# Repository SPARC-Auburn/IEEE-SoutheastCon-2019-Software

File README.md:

# Software Documentation

This is the software documentation for Auburn's IEEE Southeastcon 2019 Hardware Competition Team.  See the [main repository](https://github.com/SPARC-Auburn/IEEE-SoutheastCon-2019) for more general information.

## Robot Operating System (ROS)
The need for a simplified approach for localization sparked the switch to using the Robot Operating System (ROS.) ROS greatly simplifies complex localization, mapping, and pathfinding algorithms; all of which are incredibly essential to this competition, although, heed was taken at first because of the vast learning curve coupled with ROS. A very layman's explanation of ROS is that sensor data is input nodes, which house all the vital information for the sensors such as programs, readme files, or launch files. Nodes can talk to each other and request information, process the information, and send to another node. A graphical explanation of how our sensor nodes communicate is shown in Figure 1 below. We have four sensors; LIDAR, Camera, IMU, and encoders that create four ROS nodes. The LIDAR, IMU, and Encoder nodes all input into the localization node, this node coupled with the camera node create what we call the decision maker or essentially a path planner. The decision maker then outputs motor control commands to move the robot.

**Figure 1:** ROS Node Diagram

Figure 7 shows the resulting ROS graph of our implementation.  After testing, we determined the IMU was not adding any additional helpful information for localization so it was omitted from the final design.

**Figure 2:** ROS Node Diagram

## LIDAR and Localization

The LIDAR sensor is one of the main components of localization; this sensor acts sort of like a GPS for the robot. The YDLIDAR has a 360-degree scanning range with a 10-meter range. As stated previously and shown in Figure 1 the LIDAR will be a node, and this is one of two inputs into the localization node. ROS greatly simplifies the localization process as it already has the algorithms needed, one being AMCL. Adaptive Monte Carlo Localization is the process of tracking the pose of a robot against a known map, which is our case. AMCL takes in a map, LIDAR scan, and transform messages, and outputs pose estimates. As stated one of the first things we need to implement the AMCL algorithm is a known map, which is the competition field. Our original process of creating a map was creating a jpeg image and feeding it thru a python program launched within ROS to return a map. However, errors were given when adding the LIDAR scan data to the map.  To solve this issue, we had to pre-map the field with actual data using simultaneous location and mapping (SLAM).  This proved to be very effective, especially when there was a large skew in the field shape.  See Figure 3 for a view of the robot’s orientation and position plotted on a map in ROS.

**Figure 3:** RVIZ map with localized position and orientation

## Rotary Encoder and Odometry
In order to have more precise measurements in movement, we will use two capacitive encoders attached to the motors.  The encoders measure and count the turns of the motors, allowing us to know how far the robot will travel with one motor turn.  Using this alongside the localization and object detection, we would be able to move the robot the exact distance towards any detected object to ensure the robot picks up the object.  This will also prevent the robot from pushing any object into a position that would make it difficult to pick up.

The encoders are wired and read using a Teensy microcontroller.  The Teensy features built in interrupts that allow regular updates from the encoders.  This is required as the encoders measure rotations in ticks, these ticks update at a very fast frequency, requiring processing just as quickly.  The Teensy reads the encoder ticks and calculates the angular acceleration, which is then sent to the Raspberry Pi via serial.  
## Visual Detection
We are using the Raspberry Pi Camera Module to detect the debris objects.  By using the open-source computer vision library, the Pi can extrapolate the debris’s pixel location, pixel size, the angle from center, color, type, and approximate distance from the robot.  It uses this data to make decisions on where the robot should go.  For E-Day, we demonstrated that the robot can turn towards an object, drive until the object is right in front of it and then turn and find a different object.  The program worked really well.  The biggest issue is that the camera was pointed too far up and needed to be mounted at a lower angle.  The next step was integrating visual detection with ROS.  A custom message group was created to pass the object information to the main node for navigation.
## Navigation
Once the robot is capable of finding itself on a map with localization, it becomes necessary to plan the steps from point A to point B. There are several ROS nodes available for this that we attempted to use listed below.

* DWA (Dynamic Window Approach)
    * Smoother paths
    * Requires more computation power
* FTC (Follow the Carrot)
    * More simplistic approach, less computation
    * Does not avoid obstacles well
* Move_Basic
    * Simplest planner
    * Turn to goal, move until goal is reached
    * Not always accurate
    * Does not avoid obstacles

Ultimately, our design settled on Move_Basic, as it provided the simplest approach with parameters that were in our scope of design. Aside from Move_Basic, most path planning algorithms use a form of costmaps. These costmaps determine what path would “cost” the least in terms of time and distance. Most algorithms also use both a local costmap and a global costmap.

The local costmap will calculate where the robot should go in its immediate vicinity, this is usually calculated in real time as the range of the map is shorter and in relation the position of the robot. The global costmap will calculate a path using algorithms such as A*. Using both of these costmaps, the robot can efficiently navigate its space avoiding obstacles it can see.

## Using the System (4/25/19)
The following guide is representative of the system as of the date above. Method of start is likely to change. ALL OF THESE COMMANDS MUST BE RUN IN A LINUX TERMINAL.

The robot is run on ROS, Robotic Operating System. ROS supplies a modular system that does numerous things, but primarily allows different ‘nodes’ to operate on different computers, publishing and subscribing to different topics. In our case, that is two Raspberry Pis. The Pi’s are named d2.local (192.168.1.43) and r2.local (192.168.1.42.). While it is possible to connect to these addresses via VNC viewer, it is recommended to use the ssh command like shown below. You will need two terminal windows for accessing each Pi. (Note: Don’t use the local addresses for connecting to the Pis, use the hostnames d2.local and r2.local)

```ssh ubuntu@r2.local```

This will allow you to access the terminal for the system without bogging it down, as it is typically sensitive to graphical programs being run on it. Note that both Pis must be connected to the same network to use them independently, and AU_WiFi does not work for that. Using a Wi-Fi hotspot is recommended. If only one is able to be connected, ssh into the other via the first one over its local connection (ethernet).

Now that you are connected, you can begin to run the program. All of the ROS launch files are started via shell files, located in ieee-2019-electrical-software/launches on both Pis. 

```cd ~/ieee-2019-electrical-software/launches```

* To launch the required components for the ROS navigation stack, on d2.local, launch ./ftc.sh. 
* To launch AMCL, the move_base node, and the main algorithm node, launch ./amcl.sh on r2.local.

This will boot up the system and begin running whatever is in main_node. If you want to stop the system, it’s recommended to use the kill.py file also located in the /launches file. This way starting new nodes will not overwrite each other and create undesirable bugs.

With the system running, there are several tools ROS provides to allow you to see exactly what is going on in the system. It is recommended to run these on a separate computer or Pi with ROS installed that is connected to the network that the robot is on. This alleviates more computing power from the Pis. To ensure that your ROS computer is getting data from the robot, run the following commands:

```
cd ~/ieee-2019-electrical-software/
source ros.sh
```
* rviz – A visual GUI showing the map, current path, current location, and other useful information
    * By default, if the system is connected properly, RViz will boot up with the map server already loaded in from the roscore you connected to with source ros.sh. Allowing you to see what map is currently loaded in
    * To see other topics not listed by default, on the left pane there is a button that says “Add”, which will allow you to add topics to your view panel. In that window, the “By topic” tab will give you the current topics rviz can see that you can subscribe to. (ie. amcl_pose, current robot position)
* rqt_graph
    * Application gives a visual representation of all the nodes the roscore can see and what topics they are publishing and subscribing to.
* rostopic echo topic
    * A simple terminal output of the topic you choose
* rosnode list node
    * Lists the nodes currently running under the roscore

There are numerous commands that ROS also includes that are a bit too in depth to list here, however more information and tutorials on ROS can be found at http://wiki.ros.org/.

## Debugging (04/25/19)

The following guide is representative of the system as of the date above. Methods are subject to change as the system changes.

### “I can’t connect to either Pi”
* Plug each one in manually to a computer monitor and check that they are connected to the same network you are
* Attempt to ping the Pis via their addresses on your network. This can be checked by using ifconfig

### “RViz, RQT, etc.. can’t connect to my Pi / I can’t see any data”
* Most of the time this happens when one Pi is not connected via WiFi to your network. 
* You’ll find that the nodes run on that Pi will not be seen in the RQT graph.

### “My robot won’t localize itself after moving”
* This is an in-depth problem, as there can be many sources of error. AMCL is what allows the robot to determine where it is in the global space. It uses primarily the laser scan data and the odometry (encoders). Ensure both are outputting what you would expect with rostopic echo
* Ensure you define the correct initial position in the amcl_diff.launch file. Don’t forget the orientation (in radians)

### “The robot won’t go to the correct spot I defined”
* Ensure the position you defined is within the map space using RViz.
* There are currently several bugs with the navigation stack to be worked out. Using the move_base nodes that use costmaps seem to have the most trouble with navigation

## Known Bugs (04/25/19)
* Move_Base node is still sporadic and a primary cause of being unable to navigate the space
* The /pid_velocity nodes are currently untuned, so they have been changed to a static range of 20%-50% in motor power terms. (The robot overcomes the power of inertia at 20%) This should be fixed at some point to allow the robot to be more accurate
* AMCL sometimes will lose its position if it does not move for an extended period

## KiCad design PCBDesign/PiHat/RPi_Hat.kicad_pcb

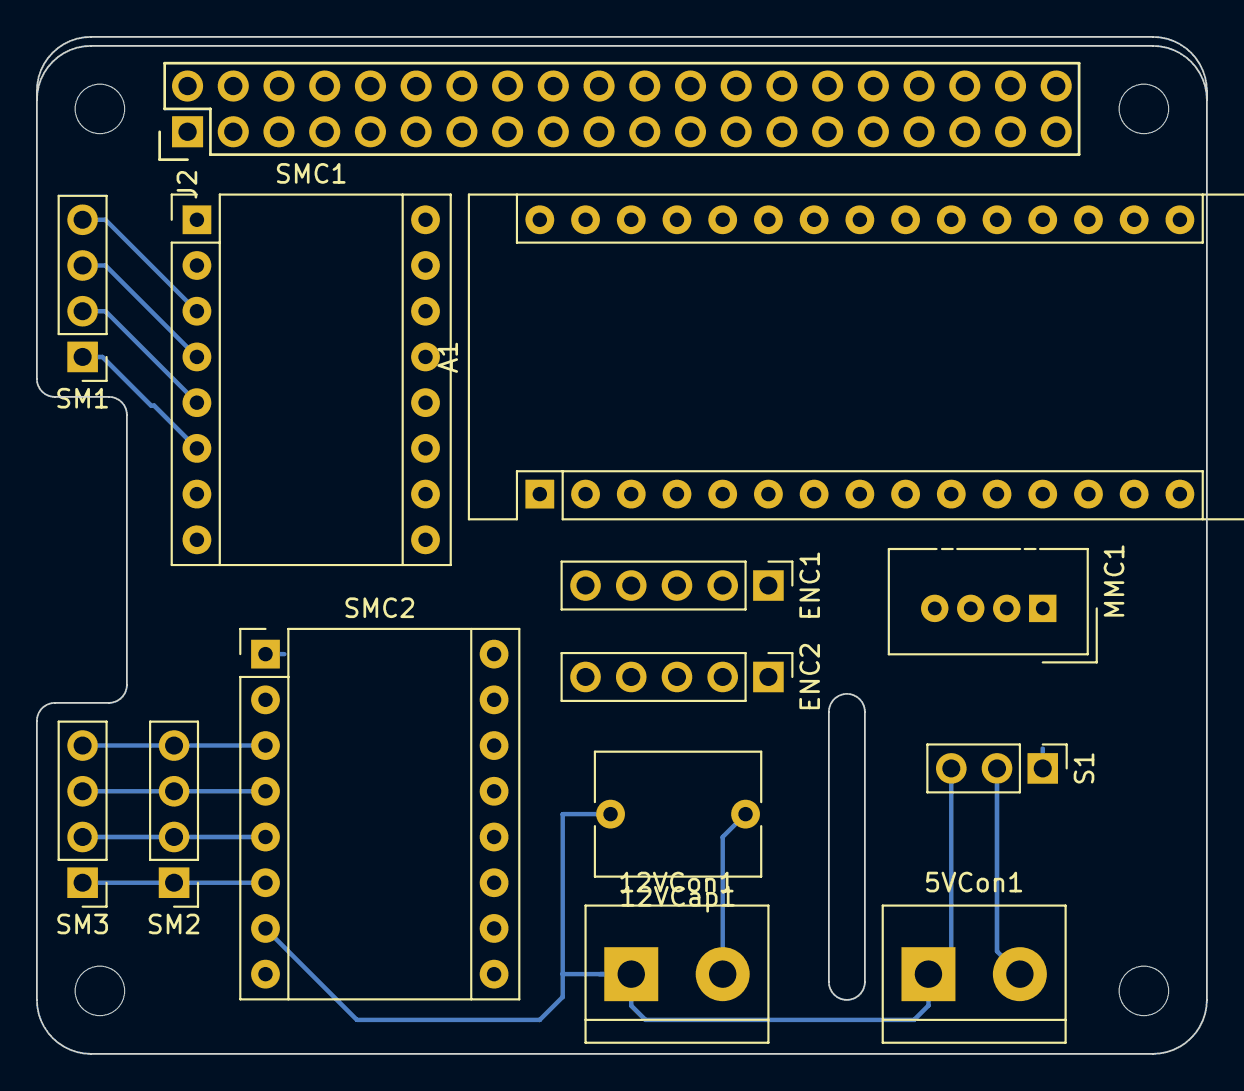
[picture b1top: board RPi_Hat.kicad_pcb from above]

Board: 2 copper layers, 65.0 x 56.5 mm, 14 parts (0 on the bottom side), 18 nets.

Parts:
5VCon1, 12VCon1: Screw_Terminal_01x02; TerminalBlock_bornier-2_P5.08mm
12VCap1: CAP; C_Rect_L9.0mm_W6.7mm_P7.50mm_MKT
A1: Arduino_Nano_v3.x; Arduino_Nano
ENC1, ENC2: Conn_01x05_Male; PinHeader_1x05_P2.54mm_Vertical
J2: RPi_GPIO; Pin_Header_Straight_2x20
MMC1: Conn_01x04_Male; NS-Tech_Grove_1x04_P2mm_Vertical
S1: Conn_01x03_Male; PinHeader_1x03_P2.54mm_Vertical
SM1, SM2, SM3: Conn_01x04_Male; PinHeader_1x04_P2.54mm_Vertical
SMC1, SMC2: Pololu_Breakout_A4988; Pololu_Breakout-16_15.2x20.3mm

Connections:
/RPi_GPIO/5V: 5VCon1.2, J2.2, S1.2, SMC1.2, SMC2.2
/RPi_GPIO/12V: 12VCap1.1, 12VCon1.2, SMC1.8, SMC2.8
/RPi_GPIO/GND: 5VCon1.1, 12VCap1.2, 12VCon1.1, J2.39, S1.3, SMC1.1, SMC1.7, SMC2.1, SMC2.7
unnamed: A1.6, S1.1
unnamed: A1.11, SMC1.16
unnamed: A1.12, SMC1.15
unnamed: A1.14, SMC2.15
unnamed: A1.15, SMC2.16
unnamed: SM1.1, SMC1.6
unnamed: SM1.2, SMC1.5
unnamed: SM1.3, SMC1.4
unnamed: SM1.4, SMC1.3
unnamed: SM2.1, SM3.1, SMC2.6
unnamed: SM2.2, SM3.2, SMC2.5
unnamed: SM2.3, SM3.3, SMC2.4
unnamed: SM2.4, SM3.4, SMC2.3
unnamed: SMC1.13, SMC1.14
unnamed: SMC2.13, SMC2.14

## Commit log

2016-02-11 Beginning of 3D Vision
2018-10-30 Added files from main repository
2018-10-30 small change to test notifications
2018-10-30 Serial code sends motor control data
2018-11-06 started main program integration
2018-11-06 Adjusted arduino program
2018-11-16 established serial control - pi side
2018-11-16 established serial control - arduino side
2018-11-16 added missing lidar files
2018-11-16 Replaced LIDAR program with correct program
2018-11-16 recorded LIDAR data on field
2018-11-23 Merged debris detection and arduino control. Ready for hardware testing.
2018-11-23 small documentation changes
2018-12-13 rudimentary localization demo
2019-01-21 Established realtime angle calculations, needs optimization
2019-01-21 Refactored vision.cpp, need to figure out atan() issue
2019-01-22 Fixed angle function, needs speed optimization.
2019-01-23 Added elapse time measurement
2019-01-24 Hopefully major speed improvements for primary vision, testing later today
2019-01-24 push to rpi
2019-01-24 working but slow :( improvements to be made
2019-01-24 eeficiency
2019-01-24 placeholder
2019-01-24 got 2 go fasttttt
2019-01-24 3.5 fps bb
2019-01-30 Fixed image display
2019-02-03 Basic look and turn program somewhat working. Need to work out test platform motor control issues.
2019-02-05 Added arduino files developed over weekend
2019-02-05 Added new motor controller library
2019-02-05 formatting and cleanup
2019-02-06 Code refactoring, added color indexor, added distance detection. Needs testing.
2019-02-06 Fixed syntax issues
2019-02-09 Added qwop control and Arduino motor driver. Needs tested.
2019-02-09 Got sensorless movement program working on new bot
2019-02-11 added updated arduino program
2019-02-12 color indexor and distance detection now working
2019-02-12 turn to cube algorithm working
2019-02-13 maybe threaded? cant compile cause ssh appears to be down
2019-02-13 Upload New File
2019-02-13 Adjusted controlMotor function, functions for gate/bar control
2019-02-13 Threaded main compiling sucessfully. hasnt been tested due to battery charge state
2019-02-14 minor changes for threading
2019-02-15 Fixed Serial Delay
    reduced the number of serial reads.
2019-02-17 Pushing Alex's motor driver changes
2019-02-17 Started merge of Alex's and Joe's programs
2019-02-17 Code cleanup and documentation.
2019-02-17 Fixed syntax issues.
2019-02-17 Fixed baud rate issue and documented code
2019-02-17 Restablished threaded turn to cube program.
2019-02-20 Minor cleanup and simplification
2019-02-20 Added a serial write function that doesn't take std::string
2019-02-20 Program exits if camera is not detected
2019-02-21 Corner detection; minor reorganization
2019-02-21 temporarily changed baud rate
2019-02-21 added testing function and changed baudrate. Having some major inconsistency serial issues
2019-02-22 Renamed Arduino file so that it opens
    The Arduino IDE on the Raspberry Pi will not open this file unless it has underscores in its name instead of dashes.
2019-02-22 Revert "Renamed Arduino file so that it opens"
    This reverts commit 844ba2a3c4a442812a88a962c574b64e783cc9fb.
    It turns out that that was just do to a very old Arduino version.
2019-02-22 New version working with jittery program. Fixed serial issues. So we think.
2019-02-22 Arduino code for jittery program
2019-02-22 Added going forward feature so that the robot fetches debris.
2019-02-25 Final E-Day Program
2019-02-28 Uploaded PiHat template
    Came from PiHat official spec
2019-02-28 Work on schematic and loading in custom footprints
2019-03-01 First design, PiHat too small for our parts
    Could possibly extend one side over the Pi
2019-03-01 Minor fixes, started on traces
    Part placement and Nano pins may need to be adjusted. Still missing: MMC and encoder schematic connections, IMU footprint and schematic connections
2019-03-06 Added Main-Program-2 directory for ROS development
2019-03-07 Established sample program works. Will start on fleshing out OpenCV -> Main_Node interface
2019-03-07 Added main_node and opencv_node. Main_node can listen to data from beginner_tutorials node and opencv_node. Need to fill in opencv_node with interface with vision.cpp from Main-Program-1.
2019-03-13 Added imu library, added launch file in main node, created custom vision message
2019-03-14 Established ROS custom node program working on Pi. See readme for instructions.
2019-03-14 Replaced submodule with corresponding files
2019-03-14 IMU working on Pi in ROS. Needs calibrated. Added debugging tools to readme.
2019-03-14 Main node can now receive data from IMU
2019-03-14 Merged vision program with vision talker node
2019-03-18 Added progress on ROS vision stuff
2019-03-20 Moved PCB design to other repository
2019-03-23 Fixed vision syntax errors
2019-03-23 Added Encoder test program
2019-03-23 Fixed most compile errors
2019-03-24 Vision Node in OpenCV is now operational!
2019-03-25 Setup .gitignore
    A lot of build files and generated files were removed from the repository. Also updated a few paths in the README.
2019-03-25 Added source for rosserial_arduino
2019-03-26 Test of Arduino communication
2019-03-26 arduino lcd prints hello from main_node
2019-03-29 added encoder program
2019-03-30 raspbian with lidar,map,amcl,rviz.
2019-03-30 Auto stash before merge of "master" and "origin/master"
2019-04-03 Odometry node that takes inputs and does all the proper transforms. Completely untested
2019-04-03 odom_Publisher Builds now
2019-04-03 IT LIVES
2019-04-03 reconfigured constants
2019-04-04 added old Arduino code into main node
2019-04-04 Arduino now working in ROS. Abandoning ROS Serial
2019-04-04 Added servo and LCD communication to Arduino Serial
    Movement test program added, but not yet tested on bot. Likely still small syntax errors
2019-04-04 Small adjustment because why not
2019-04-04 Fixed sketch errors
    Sorry for all the pushes
2019-04-05 Motors running, servos move, LCD to come soon
2019-04-05 Arduino code for changes
    LCD output almost done, servo input still needs to be unsigned char
2019-04-05 Bug fixes to try tomorrow and publish go button state
    Don't hate me
2019-04-05 LCD and servo output working, Arduino buffer needs to be reset
2019-04-05 Arduino LCD and servo code
    Hit the reset button before running code to clear the buffer. Now working on button publishing
2019-04-05 Go push button operational
2019-04-05 Arduino code for push button
    Adding initial pose buttons should be trivial
2019-04-05 initialpose and some arduino stuff
2019-04-06 Finished initial debris locations
2019-04-06 misc changes, yeehaw. Just doing this so I can pull
2019-04-06 Odometry publisher that uses serial and nano slaves rather than the polling atrocity
2019-04-06 added potentiometer mode selector test program
2019-04-06 Arduino communication to button, pot, LCD, and servos working
2019-04-06 Arduino code for last push
    Dunzo.. for now
2019-04-06 Serial odom working and razor stuff
2019-04-07 IT WORKSish
2019-04-07 diffdrive and stuff
2019-04-07 reee
2019-04-07 Take ??? on Arduino Serial
    Hopefully this fixes some things
2019-04-08 added back odom publisher
2019-04-08 Much more robust corner detection
    Position of corner is calculated but currently inaccurate
2019-04-08 Minor cleanup
    Changed some constants from macros to actual constants.
2019-04-08 Arduino 'Robust' Serial upload
    Some preliminary code- uploading to test on Pi
2019-04-08 Revert "Arduino 'Robust' Serial upload"
    This reverts commit 280381a56c8338c711363a43c0b859bef1a4bc5d.
2019-04-08 Navigation stack launch files and config
2019-04-08 removed
2019-04-08 The Alex Jones late night show
2019-04-08 Actual 2dnav thing, 'roslaunch move_base.launch'
2019-04-08 Josh forgot a 0
2019-04-08 Improved color thresholds
2019-04-08 Removed extra newlines in output
2019-04-09 Fix CMake Files, add some code for setting goals
2019-04-09 added initialPosePublisher
2019-04-09 attempted to fix initialPos
2019-04-09 3D vision is a bit more accurate.
2019-04-09 moveFwdOneMeter() goal added, uncomment to use
2019-04-09 diff drive added and working
2019-04-09 Main node receives position in robot coordinates
2019-04-09 It can do loop-de-loops now
2019-04-09 Main_node can find the closest object of a color
2019-04-09 removed init pose from main
2019-04-09 removed endls that spammed to hell
2019-04-09 oopsies
2019-04-09 oopsies pt 2
2019-04-09 Everything launches.
2019-04-09 initial loc test
2019-04-09 localization?
2019-04-09 josh changes
2019-04-09 Various improvements to vision
2019-04-10 changed color conventions
2019-04-10 added basic block getting and orbit code, doesnt recieve robot's actual pos
2019-04-11 Changed goal params
    -Josh
2019-04-11 tweaked come localization jazz
2019-04-11 pushing this to compile shit, wouldnt revert to this commit if I were you
2019-04-11 trying to compile
2019-04-11 trying to compile2
2019-04-11 this compiles now
2019-04-11 changed the color selection scheme
2019-04-11 slight change to compile
2019-04-11 trying to launch file
2019-04-11 added some python arduino stuff to test
2019-04-11 better serial?
2019-04-11 set initial flag and gate position in setup()
2019-04-11 Save of vision work
2019-04-11 Memes
2019-04-11 fixed arduino flag control and reduced the main, havent compiled main
2019-04-11 moving arduino reading duties to other python script, added subscribers, needs to be tested
2019-04-11 bad py serial
2019-04-11 bad serial part 2
2019-04-11 main node compiles
2019-04-12 Changed move_base to use DWA planner
    Better for fast moving robots with more processing power. We have that with the new Pi
2019-04-12 added arduino_talker
2019-04-12 edited the main.cpp to publish to the arduino control
2019-04-12 Added subscribe to desired color
2019-04-12 added color passthrough in main
2019-04-12 launch files. yeeeeett
2019-04-12 added moveBaseTest
2019-04-12 Finds corners in at least one scenario
2019-04-12 Added spacetels map
    Changed nothing else- in Main-Program/mymap
2019-04-12 merge
2019-04-12 working main
2019-04-12 sync
2019-04-12 blocks within .2m of the octet are ignored
2019-04-12 reduced publish rate for startFunc and colorFunc
2019-04-12 working arduino code
2019-04-13 Carrot
2019-04-13 Accurate vision distance for new bot
    Also fixed some issues in vision node
2019-04-13 clock!
2019-04-13 corrected types for flag and gate and removed ac.waitForGoalMet
2019-04-13 actually fixed the arduino talker type error
2019-04-13 fuck git
2019-04-13 working r2
2019-04-13 changed arduino_talker to retardation
2019-04-17 Added competition programs.
2019-04-22 D2 push
2019-04-30 git not working
2019-05-01 added information to readme
2019-05-02 added pictures to readme
